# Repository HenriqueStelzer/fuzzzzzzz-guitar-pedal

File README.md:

# Fuzzzzzzz - A guitar pedal
### My take on the classic fuzz face circuit
The Fuzzzzzzz is a fuzz face-inspired guitar pedal, redesigned with an inverting gain stage, asymmetric hard clipping, and a 720Hz high-pass tone control to sit between the reactivity of a classic fuzz and the control of a modern overdrive. This is a fully analog circuit with no microcontroller or firmware — there is no code involved. It works great on bass too.

## Table of Contents

1. [Features](#features)
2. [Circuit Overview](#circuit-overview)
3. [Usage](#usage)
   - [Connections](#connections)
   - [Turning the Effect On and Off](#turning-the-effect-on-and-off)
   - [The Knobs](#the-knobs)
   - [Tips & Tricks](#tips--tricks)
   - [Modding](#modding)
4. [Bill of Materials (BOM)](#bill-of-materials-bom)
5. [Off-Board Bill of Materials](#off-board-bill-of-materials-bom)
6. [Assembly](#assembly)
   - [Tools Required](#tools-required)
   - [Step 1 — Populate the PCB](#step-1--populate-the-pcb)
   - [Step 2 — Drill the Enclosure](#step-2--drill-the-enclosure)
   - [Step 3 — Mount the PCB](#step-3--mount-the-pcb)
   - [Step 4 — Install Off-Board Components](#step-4--install-off-board-components)
   - [Step 5 — Wire Off-Board Components to the PCB](#step-5--wire-off-board-components-to-the-pcb)
   - [Step 6 — Wire the 3PDT Footswitch](#step-6--wire-the-3pdt-footswitch-true-bypass)
   - [Step 7 — Test Before Closing](#step-7--test-before-closing)
   - [Step 8 — Close the Enclosure](#step-8--close-the-enclosure)

## Features
* Three control knobs for gain, tone control and output level
* Asymmetric clipping
* True bypass
* Quality 9V power decoupling
* Plenty of room for modding

## Circuit Overview
  The circuit is composed of a gain controlling input stage with a controllable inverting amplifier that buffers and boosts the signal with a gain ranging from 6dB to 21.6dB. The gain stage has a topology inspired by the classic fuzz face guitar pedal but modded to have a lower noise floor, use common components and a slightly different flavor of clipping. The output stage consists of a recovery/buffering stage with tone control for boosting high-mid frequencies and a final output level control.
```
In → Input buffer → Gain control → Modified fuzz clipping stage → Tone Control → Output Buffer → Out
```
## Usage
### Connections

| Jack | Connect to |
|------|-----------|
| **Input (J1)** | Your guitar or bass |
| **Output (J2)** | Your amplifier or next pedal in chain |
| **Power (J3)** | 9V DC, center-negative, 2.1mm barrel (standard Boss-style adapter) |

Current draw is very low (~10mA), so any pedalboard power supply will work fine. A 9V battery via the snap adapter (BAT1) is also supported.

### Turning the Effect On and Off

Stomp **SW1** to toggle the effect on and off. The **LED (D4)** lights up when the effect is active. When bypassed, your signal passes directly from input to output with zero coloration — this pedal uses **true bypass**.

### The Knobs

**Gain (RV1)**
Controls the amount of fuzz and drive. At minimum, expect a light, responsive crunch. At maximum, full aggressive fuzz with heavy harmonic saturation. For most playing styles, the sweet spot sits around **2–3 o'clock**.

**Tone (RV2)**
A high-mid boost control centered around **720Hz** — not a traditional treble cut like a Big Muff. Turning it up adds bite and presence; turning it down gives a warmer, rounder character. It won't get muddy at low settings.

**Level (RV3)**
Sets the output volume. Unity gain — matching your dry signal level — is roughly at **noon**. Go past that to push your amp harder.

### Tips & Tricks

- **Bass players:** the 720Hz high-pass filter keeps the low end tight and defined, making this pedal unusually bass-friendly for a fuzz.
- **Extreme settings:** stacking Gain and Tone both at maximum gives a very aggressive, almost synth-like fuzz character.
- **Guitar volume trick:** like a classic fuzz face, this pedal is sensitive to your guitar's volume knob. Rolling it back cleans up the tone significantly without touching the pedal — use this to your advantage.

### Modding

The pedal was designed with experimentation in mind. Some starting points:

- **Clipping diodes (D1, D2):** Swap the 1N4148s for germanium diodes (1N34A, OA85) for a softer, warmer clipping character with lower threshold voltage.
- **Tone center frequency:** C5 (47nF) sets the 720Hz high-pass corner of the tone control. Increasing the value shifts the center lower for a darker sound; decreasing it pushes it higher for more treble bite.
- **Gain range:** R7 (4K7) sets the minimum gain of the inverting stage. Reducing it lowers the floor for a cleaner minimum gain setting.

---

### Bill of Materials (BOM)
| **#** | **Reference**     | **Qty** | **Value** | **Footprint**                                                       | **Description**                                                  |
|-------|-------------------|---------|-----------|---------------------------------------------------------------------|------------------------------------------------------------------|
| 1     | C1, C10, C12, C15 | 4       | 100nF     | Capacitor_THT:C_Rect_L7.0mm_W2.5mm_P5.00mm                          | Unpolarized capacitor                                            |
| 2     | C2                | 1       | 4u7       | Capacitor_THT:CP_Radial_D5.0mm_P2.50mm                              | Polarized capacitor                                              |
| 3     | C3                | 1       | 100pF     | Capacitor_THT:C_Disc_D5.0mm_W2.5mm_P5.00mm                          | Unpolarized capacitor                                            |
| 4     | C4                | 1       | 2n2       | Capacitor_THT:C_Rect_L7.0mm_W2.5mm_P5.00mm                          | Unpolarized capacitor                                            |
| 5     | C5                | 1       | 47nF      | Capacitor_THT:C_Rect_L7.0mm_W2.5mm_P5.00mm                          | Unpolarized capacitor                                            |
| 6     | C6                | 1       | 47uF      | Capacitor_THT:CP_Radial_D5.0mm_P2.50mm                              | Polarized capacitor                                              |
| 7     | C7                | 1       | 4n7       | Capacitor_THT:C_Rect_L7.0mm_W2.5mm_P5.00mm                          | Unpolarized capacitor                                            |
| 8     | C8                | 1       | 22nF      | Capacitor_THT:C_Rect_L7.0mm_W2.5mm_P5.00mm                          | Unpolarized capacitor                                            |
| 9     | C9                | 1       | 10nF      | Capacitor_THT:C_Rect_L7.0mm_W2.5mm_P5.00mm                          | Unpolarized capacitor                                            |
| 10    | C11               | 1       | 1uF       | Capacitor_THT:C_Rect_L7.0mm_W2.5mm_P5.00mm                          | Unpolarized capacitor                                            |
| 11    | C13               | 1       | 100uF     | Capacitor_THT:CP_Radial_D6.3mm_P2.50mm                              | Polarized capacitor                                              |
| 12    | C14               | 1       | 10uF      | Capacitor_THT:CP_Radial_D5.0mm_P2.50mm                              | Polarized capacitor                                              |
| 13    | D1, D2            | 2       | 1N4148    | Diode_THT:D_DO-35_SOD27_P7.62mm_Horizontal                          | 100V 0.15A standard switching diode, DO-35                       |
| 14    | D3               | 1       | 1N5819    | Diode_THT:D_DO-41_SOD81_P10.16mm_Horizontal                         | 40V 1A Schottky Barrier Rectifier Diode, DO-41                   |
| 15    | D4               | 1       | LED       | LED_THT:LED_D3.0mm                                                  | Light emitting diode                                             |
| 16    | Q1               | 1       | 2N5088    | Package_TO_SOT_THT:TO-92_Inline                                     | 0.2A Ic, 40V Vce, Small Signal NPN Transistor, TO-92             |
| 17    | Q2               | 1       | 2N4401    | Package_TO_SOT_THT:TO-92_Inline                                     | 0.2A Ic, 40V Vce, Small Signal NPN Transistor, TO-92             |
| 18    | R1, R15           | 2       | 1M        | Resistor_THT:R_Axial_DIN0207_L6.3mm_D2.5mm_P7.62mm_Horizontal       | Resistor 1/4W                                                    |
| 19    | R2-R4, R12        | 4       | 10K       | Resistor_THT:R_Axial_DIN0207_L6.3mm_D2.5mm_P7.62mm_Horizontal       | Resistor 1/4W                                                    |
| 20    | R5, R10           | 2       | 100K      | Resistor_THT:R_Axial_DIN0207_L6.3mm_D2.5mm_P7.62mm_Horizontal       | Resistor 1/4W                                                    |
| 21    | R6                | 1       | 220R      | Resistor_THT:R_Axial_DIN0207_L6.3mm_D2.5mm_P7.62mm_Horizontal       | Resistor 1/4W                                                    |
| 22    | R7                | 1       | 4K7       | Resistor_THT:R_Axial_DIN0207_L6.3mm_D2.5mm_P7.62mm_Horizontal       | Resistor 1/4W                                                    |
| 23    | R8, R13           | 2       | 2K2       | Resistor_THT:R_Axial_DIN0207_L6.3mm_D2.5mm_P7.62mm_Horizontal       | Resistor 1/4W                                                    |
| 24    | R9                | 1       | 1K        | Resistor_THT:R_Axial_DIN0207_L6.3mm_D2.5mm_P7.62mm_Horizontal       | Resistor 1/4W                                                    |
| 25    | R11               | 1       | 1K5       | Resistor_THT:R_Axial_DIN0207_L6.3mm_D2.5mm_P7.62mm_Horizontal       | Resistor 1/4W                                                    |
| 26    | R14               | 1       | 33K       | Resistor_THT:R_Axial_DIN0207_L6.3mm_D2.5mm_P7.62mm_Horizontal       | Resistor 1/4W                                                    |
| 27    | R16              | 1       | 47R       | Resistor_THT:R_Axial_DIN0309_L9.0mm_D3.2mm_P12.70mm_Horizontal      | Resistor 1/2W                                                    |
| 28    | R17, R18          | 2       | 220K      | Resistor_THT:R_Axial_DIN0207_L6.3mm_D2.5mm_P7.62mm_Horizontal       | Resistor 1/4W                                                    |
| 29    | R19              | 1       | 4K7       | Resistor_THT:R_Axial_DIN0309_L9.0mm_D3.2mm_P12.70mm_Horizontal      | Resistor 1/2W                                                    |
| 30    | RV1-RV3          | 3       | 100KA     | Potentiometer_THT:Potentiometer_Alpha_RD901F-40-00D_Single_Vertical | Potentiometer                                                    |
| 31    | U1               | 1       | JRC4558   | Package_DIP:DIP-8_W7.62mm_Socket                                    | Dual General Purpose, Operational Amplifier, DIP-8/SOIC-8/SSOP-8 |

# Off-Board Bill of Materials (BOM)
| **#** | **Reference** | **Qty** | **Value**                  | **Description**                                          |
|-------|---------------|---------|----------------------------|----------------------------------------------------------|
| 1     | CASE          | 1       | Hammond 1590BB             | Diecast aluminum enclosure 119x94x34mm                   |
| 2     | J1            | 1       | 6.35mm Jack – Input        | Mono 1/4" TS input jack                                  |
| 3     | J2            | 1       | 6.35mm Jack – Output       | Mono 1/4" TS output jack                                 |
| 4     | J3            | 1       | DC Power Jack 2.1mm        | Barrel connector 2.1mm center-neg (3 poles)              |
| 5     | SW1           | 1       | 3PDT Footswitch            | Latching 3PDT stomp switch for true bypass               |
| 6     | BAT1          | 1       | 9V Battery Snap Adapter    | 9V battery clip with leads                               |
| 7     | HW1           | 4       | M3×30mm Screw              | M3 machine screw, 30mm length                            |
| 8     | HW2           | 12      | M3 Nut                     | M3 hex nut                                               |

---

## Assembly

### Tools Required

- Soldering iron and solder
- Wire cutters and strippers
- Small flathead and Phillips screwdrivers
- Drill and step bit (for enclosure drilling)
- Multimeter (recommended for testing)

### Step 1 — Populate the PCB

Solder components onto the PCB in this order, from shortest to tallest, so taller parts don't get in the way:

1. **Resistors** (R1–R19)
2. **Small capacitors** — ceramic and film (C1, C3, C4, C5, C7, C8, C9, C10, C11, C12, C15)
3. **Diodes** (D1, D2, D3) — the stripe on the body marks the cathode; match it to the marking on the PCB silkscreen
4. **Transistors** (Q1, Q2) — 2N5088 at Q1, 2N4401 at Q2; match the flat face of the TO-92 body to the silkscreen
5. **IC socket** for U1 — solder the socket, not the IC itself
6. **Electrolytic capacitors** (C2, C6, C13, C14) — the longer leg is positive; match it to the `+` marking on the PCB
7. **Potentiometers** (RV1, RV2, RV3)

Once all PCB soldering is done, insert the **JRC4558** into its socket. Never solder the IC directly — heat damages it.

### Step 2 — Drill the Enclosure

Mark and drill the **Hammond 1590BB** enclosure for:

- 3× potentiometer holes (top face)
- 1× LED hole (top face)
- 1× footswitch hole (top face, center)
- 2× 6.35mm jack holes (left and right sides)
- 1× DC barrel jack hole (top or back panel)
- 4× M3 mounting holes for the PCB (matching your PCB layout)

Deburr all holes after drilling to avoid sharp edges cutting into wiring later.

### Step 3 — Mount the PCB

Mount the PCB inside the enclosure using the M3 hardware in this arrangement:
```
Screw head → Case wall → Nut ··· Nut → PCB → Nut
```

This sandwiches the enclosure wall between two nuts and the PCB between two more, keeping everything rigid. Use all **4× M3×30mm screws** and **12× M3 nuts**.

> The rubber feet that come with the Hammond enclosure sit taller than the M3 screw heads, so the screws won't scratch any surface the pedal rests on.

### Step 4 — Install Off-Board Components

Mount and hand-tighten into their drilled holes:

- **J1** — Input jack (left side)
- **J2** — Output jack (right side)
- **J3** — DC power jack
- **SW1** — 3PDT footswitch
- **D4** — LED through the top panel hole; secure with a bezel if desired
- **BAT1** — Route the battery snap adapter inside the enclosure

### Step 5 — Wire Off-Board Components to the PCB

Use short, neat runs of hookup wire. Refer to the schematic for exact pad labels.

#### Power

Connect both the DC jack and the battery snap to the PCB's power input pads. Observe polarity — this pedal uses **center-negative** power, which is standard for guitar pedals. D3 (1N5819) on the PCB provides reverse polarity protection, but always double-check before powering on.

#### Audio Jacks

- J1 tip → PCB `IN` pad; J1 sleeve → GND
- J2 tip → PCB `OUT` pad (via SW1, see below); J2 sleeve → GND

### Step 6 — Wire the 3PDT Footswitch (True Bypass)

The 3PDT switch has 9 lugs arranged in a 3×3 grid. Looking at the switch from the **back** (solder side), number them like this:
```
[ 1 ][ 2 ][ 3 ]
[ 4 ][ 5 ][ 6 ]   ← middle row: commons
[ 7 ][ 8 ][ 9 ]
```

The **middle row** (lugs 4, 5, 6) are the commons — they always carry the signal. The top and bottom rows are the throws — which row the common connects to depends on whether the switch is stomped or not.

Wire it as follows:

| Lug | Connection |
|-----|-----------|
| **1** | PCB `IN` pad |
| **2** | PCB `OUT` pad |
| **3** | LED anode (D4 `+`) |
| **4** | Input jack (J1) tip |
| **5** | Output jack (J2) tip |
| **6** | +9V supply |
| **7** | Bridge to lug 8 with a short wire |
| **8** | Bridge to lug 7 with a short wire |
| **9** | Leave unconnected |

> **Note:** The LED current-limiting resistor (R6, 220Ω) is already on the PCB, so connect lug 3 directly to the LED anode without adding any extra resistor inline.

#### How it works

**Effect ON (LED lit):** The commons (4, 5, 6) connect to the top row (1, 2, 3).
- Lug 4 → Lug 1: Guitar signal goes into the PCB
- Lug 5 → Lug 2: PCB output goes to the amp
- Lug 6 → Lug 3: +9V reaches the LED → LED lights up

**Effect OFF (bypassed):** The commons (4, 5, 6) connect to the bottom row (7, 8, 9).
- Lug 4 → Lug 7, bridged to Lug 8 → Lug 5: Guitar signal goes directly to the amp, skipping the PCB entirely
- Lug 6 → Lug 9: +9V goes nowhere → LED off

This is **true bypass** — when off, the PCB is completely out of the signal path.

### Step 7 — Test Before Closing

Before screwing the enclosure shut:

1. Power the pedal via a 9V adapter
2. Plug a guitar into J1 and an amp into J2
3. Stomp SW1 — the LED should light up and you should hear the fuzz effect
4. Stomp again — the LED should go off and the signal should pass clean with no coloration
5. Turn each knob through its full range and listen for scratchiness or dropouts

If you have a multimeter, probe the test points on the PCB to verify the bias voltages on Q1 and Q2 match the schematic.

### Step 8 — Close the Enclosure

Once everything checks out, tuck all wiring neatly inside the enclosure, seat the battery, and screw the lid shut. Your Fuzzzzzzz is ready to play.

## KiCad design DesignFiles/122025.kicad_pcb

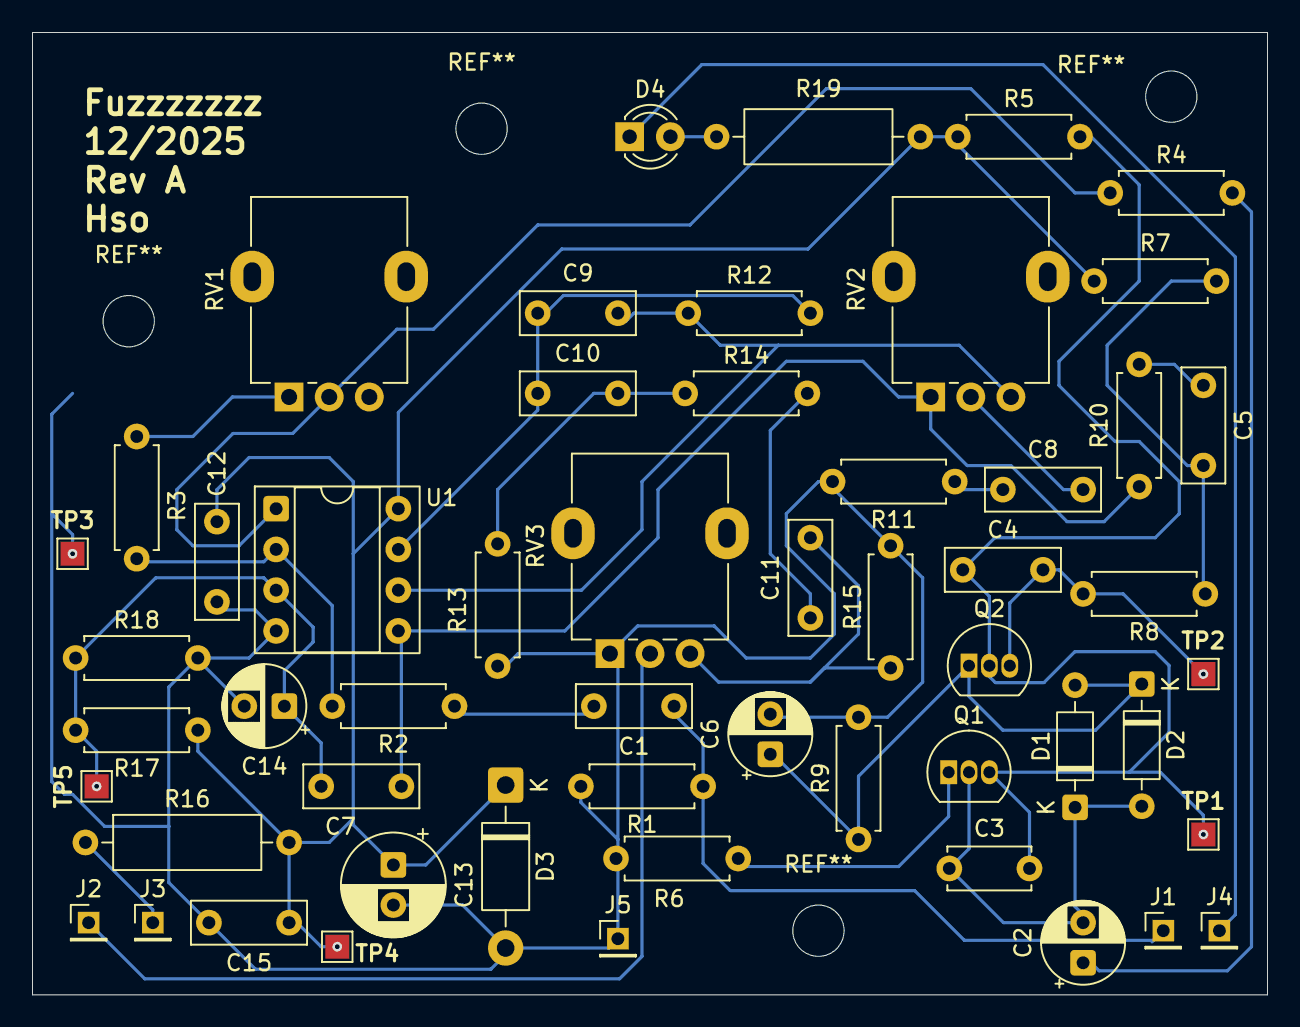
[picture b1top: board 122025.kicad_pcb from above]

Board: 2 copper layers, 77.0 x 60.0 mm, 54 parts (0 on the bottom side), 28 nets.

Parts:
C1, C10, C12, C15: 100nF; C_Rect_L7.0mm_W2.5mm_P5.00mm
C2: 4u7; CP_Radial_D5.0mm_P2.50mm
C3: 100pF; C_Disc_D5.0mm_W2.5mm_P5.00mm
C4: 2n2; C_Rect_L7.0mm_W2.5mm_P5.00mm
C5: 47nF; C_Rect_L7.0mm_W2.5mm_P5.00mm
C6: 47uF; CP_Radial_D5.0mm_P2.50mm
C7: 4n7; C_Rect_L7.0mm_W2.5mm_P5.00mm
C8: 22nF; C_Rect_L7.0mm_W2.5mm_P5.00mm
C9: 10nF; C_Rect_L7.0mm_W2.5mm_P5.00mm
C11: 1uF; C_Rect_L7.0mm_W2.5mm_P5.00mm
C13: 100uF; CP_Radial_D6.3mm_P2.50mm
C14: 10uF; CP_Radial_D5.0mm_P2.50mm
D1, D2: 1N4148; D_DO-35_SOD27_P7.62mm_Horizontal
D3: 1N5819; D_DO-41_SOD81_P10.16mm_Horizontal
D4: LED; LED_D3.0mm
J1: IN; PinHeader_1x01_P2.00mm_Vertical
J2: OUT; PinHeader_1x01_P2.00mm_Vertical
J3: PWR; PinHeader_1x01_P2.00mm_Vertical
J4: LED; PinHeader_1x01_P2.00mm_Vertical
J5: GND; PinHeader_1x01_P2.00mm_Vertical
Q1: 2N5088; TO-92_Inline
Q2: 2N4401; TO-92_Inline
R1, R15: 1M; R_Axial_DIN0207_L6.3mm_D2.5mm_P7.62mm_Horizontal
R2, R3, R4, R12: 10K; R_Axial_DIN0207_L6.3mm_D2.5mm_P7.62mm_Horizontal
R5, R10: 100K; R_Axial_DIN0207_L6.3mm_D2.5mm_P7.62mm_Horizontal
R6: 220R; R_Axial_DIN0207_L6.3mm_D2.5mm_P7.62mm_Horizontal
R7: 4K7; R_Axial_DIN0207_L6.3mm_D2.5mm_P7.62mm_Horizontal
R8, R13: 2K2; R_Axial_DIN0207_L6.3mm_D2.5mm_P7.62mm_Horizontal
R9: 1K; R_Axial_DIN0207_L6.3mm_D2.5mm_P7.62mm_Horizontal
R11: 1K5; R_Axial_DIN0207_L6.3mm_D2.5mm_P7.62mm_Horizontal
R14: 33K; R_Axial_DIN0207_L6.3mm_D2.5mm_P7.62mm_Horizontal
R16: 47R; R_Axial_DIN0309_L9.0mm_D3.2mm_P12.70mm_Horizontal
R17, R18: 220K; R_Axial_DIN0207_L6.3mm_D2.5mm_P7.62mm_Horizontal
R19: 4K7; R_Axial_DIN0309_L9.0mm_D3.2mm_P12.70mm_Horizontal
RV1, RV2, RV3: 100KA; Potentiometer_Alpha_RD901F-40-00D_Single_Vertical
TP1: 0.7V; TestPoint_Pad_1.5x1.5mmDoubleSided
TP2, TP5: 4.5V; TestPoint_Pad_1.5x1.5mmDoubleSided
TP3: 0V; TestPoint_Pad_1.5x1.5mmDoubleSided
TP4: 9V; TestPoint_Pad_1.5x1.5mmDoubleSided
U1: JRC4558; DIP-8_W7.62mm_Socket

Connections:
/In: C1.1, J1.1, R1.1
/LED GND: D4.1 (K), J4.1
/Out: J2.1, RV3.2
/Power Jack: J3.1, R16.1
/V+: C12.1, C13.1, C15.1, D3.1 (K), R5.1, R7.1, R16.2, R17.1, R19.1, TP4.1, U1.8 (V+)
/Vref: C7.1, C14.1, R17.2, R18.1, TP5.1, U1.3 (+)
GND: C6.2, C12.2, C13.2, C14.2, C15.2, D3.2 (A), J5.1, R1.2, R6.1, R9.2, R11.2, R13.2, R15.2, R18.2, RV3.1, TP3.1, U1.4 (V-)
unnamed: C1.2, R2.1
unnamed: C2.1, R4.2
unnamed: C5.1, R7.2, R8.1
unnamed: C5.2, R10.1
unnamed: C8.1, R11.1
unnamed: C8.2, RV2.2
unnamed: C9.2, C10.1, R12.2, U1.7
unnamed: C10.2, R13.1, R14.1
unnamed: C11.1, R14.2
unnamed: C11.2, R15.1, RV3.3
unnamed: C6.1, D1.2 (A), D2.1 (K), Q2.1 (E), R9.1
unnamed: C2.2, C3.1, D1.1 (K), D2.2 (A), Q1.2 (B)
unnamed: D4.2 (A), R19.2
unnamed: C3.2, C4.1, Q1.3 (C), Q2.2 (B), R5.2, TP1.1
unnamed: Q1.1 (E), R6.2
unnamed: C4.2, Q2.3 (C), R8.2, TP2.1
unnamed: R3.2, RV1.1
unnamed: R4.1, RV1.2, U1.1
unnamed: R2.2, R3.1, U1.2 (-)
unnamed: C7.2, R10.2, RV2.1, U1.5 (+)
unnamed: C9.1, R12.1, RV2.3, U1.6 (-)

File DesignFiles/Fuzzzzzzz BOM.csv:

Reference,Qty,Value,Footprint,Description
"C1, C10, C12, C15",4,100nF,Capacitor_THT:C_Rect_L7.0mm_W2.5mm_P5.00mm,Unpolarized capacitor
C2,1,4u7,Capacitor_THT:CP_Radial_D5.0mm_P2.50mm,Polarized capacitor
C3,1,100pF,Capacitor_THT:C_Disc_D5.0mm_W2.5mm_P5.00mm,Unpolarized capacitor
C4,1,2n2,Capacitor_THT:C_Rect_L7.0mm_W2.5mm_P5.00mm,Unpolarized capacitor
C5,1,47nF,Capacitor_THT:C_Rect_L7.0mm_W2.5mm_P5.00mm,Unpolarized capacitor
C6,1,47uF,Capacitor_THT:CP_Radial_D5.0mm_P2.50mm,Polarized capacitor
C7,1,4n7,Capacitor_THT:C_Rect_L7.0mm_W2.5mm_P5.00mm,Unpolarized capacitor
C8,1,22nF,Capacitor_THT:C_Rect_L7.0mm_W2.5mm_P5.00mm,Unpolarized capacitor
C9,1,10nF,Capacitor_THT:C_Rect_L7.0mm_W2.5mm_P5.00mm,Unpolarized capacitor
C11,1,1uF,Capacitor_THT:C_Rect_L7.0mm_W2.5mm_P5.00mm,Unpolarized capacitor
C13,1,100uF,Capacitor_THT:CP_Radial_D6.3mm_P2.50mm,Polarized capacitor
C14,1,10uF,Capacitor_THT:CP_Radial_D5.0mm_P2.50mm,Polarized capacitor
"D1, D2",2,1N4148,Diode_THT:D_DO-35_SOD27_P7.62mm_Horizontal,"100V 0.15A standard switching diode, DO-35"
D3,1,1N5819,Diode_THT:D_DO-41_SOD81_P10.16mm_Horizontal,"40V 1A Schottky Barrier Rectifier Diode, DO-41"
D4,1,LED,LED_THT:LED_D3.0mm,Light emitting diode
Q1,1,2N5088,Package_TO_SOT_THT:TO-92_Inline,"0.2A Ic, 40V Vce, Small Signal NPN Transistor, TO-92"
Q2,1,2N4401,Package_TO_SOT_THT:TO-92_Inline,"0.2A Ic, 40V Vce, Small Signal NPN Transistor, TO-92"
"R1, R15",2,1M,Resistor_THT:R_Axial_DIN0207_L6.3mm_D2.5mm_P7.62mm_Horizontal,Resistor 1/4W
"R2-R4, R12",4,10K,Resistor_THT:R_Axial_DIN0207_L6.3mm_D2.5mm_P7.62mm_Horizontal,Resistor 1/4W
"R5, R10",2,100K,Resistor_THT:R_Axial_DIN0207_L6.3mm_D2.5mm_P7.62mm_Horizontal,Resistor 1/4W
R6,1,220R,Resistor_THT:R_Axial_DIN0207_L6.3mm_D2.5mm_P7.62mm_Horizontal,Resistor 1/4W
R7,1,4K7,Resistor_THT:R_Axial_DIN0207_L6.3mm_D2.5mm_P7.62mm_Horizontal,Resistor 1/4W
"R8, R13",2,2K2,Resistor_THT:R_Axial_DIN0207_L6.3mm_D2.5mm_P7.62mm_Horizontal,Resistor 1/4W
R9,1,1K,Resistor_THT:R_Axial_DIN0207_L6.3mm_D2.5mm_P7.62mm_Horizontal,Resistor 1/4W
R11,1,1K5,Resistor_THT:R_Axial_DIN0207_L6.3mm_D2.5mm_P7.62mm_Horizontal,Resistor 1/4W
R14,1,33K,Resistor_THT:R_Axial_DIN0207_L6.3mm_D2.5mm_P7.62mm_Horizontal,Resistor 1/4W
R16,1,47R,Resistor_THT:R_Axial_DIN0309_L9.0mm_D3.2mm_P12.70mm_Horizontal,Resistor 1/2W
"R17, R18",2,220K,Resistor_THT:R_Axial_DIN0207_L6.3mm_D2.5mm_P7.62mm_Horizontal,Resistor 1/4W
R19,1,4K7,Resistor_THT:R_Axial_DIN0309_L9.0mm_D3.2mm_P12.70mm_Horizontal,Resistor 1/2W
RV1-RV3,3,100KA,Potentiometer_THT:Potentiometer_Alpha_RD901F-40-00D_Single_Vertical,Potentiometer
U1,1,JRC4558,Package_DIP:DIP-8_W7.62mm_Socket,"Dual General Purpose, Operational Amplifier, DIP-8/SOIC-8/SSOP-8"

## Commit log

2025-12-22 First upload
    Missing tone control and no pcb yet.
2025-12-26 Added tone and propper gain control
2025-12-29 Add README with project description
2026-01-14 Minor corrections in README.md
2026-01-14 Added schematic image
2026-03-05 Add Off-Board BOM section to README
    Added Off-Board Bill of Materials (BOM) section with components and descriptions.
2026-03-21 Add hardware components to README
2026-03-21 Update hardware quantities in README
2026-04-01 Enhance README with features and assembly instructions
    Expanded the README to include detailed features, usage instructions, and assembly steps for the Fuzzzzzzz guitar pedal.
2026-04-01 Clarify that circuit is fully analog with no code
    Added clarification that the circuit is fully analog with no microcontroller or firmware.
